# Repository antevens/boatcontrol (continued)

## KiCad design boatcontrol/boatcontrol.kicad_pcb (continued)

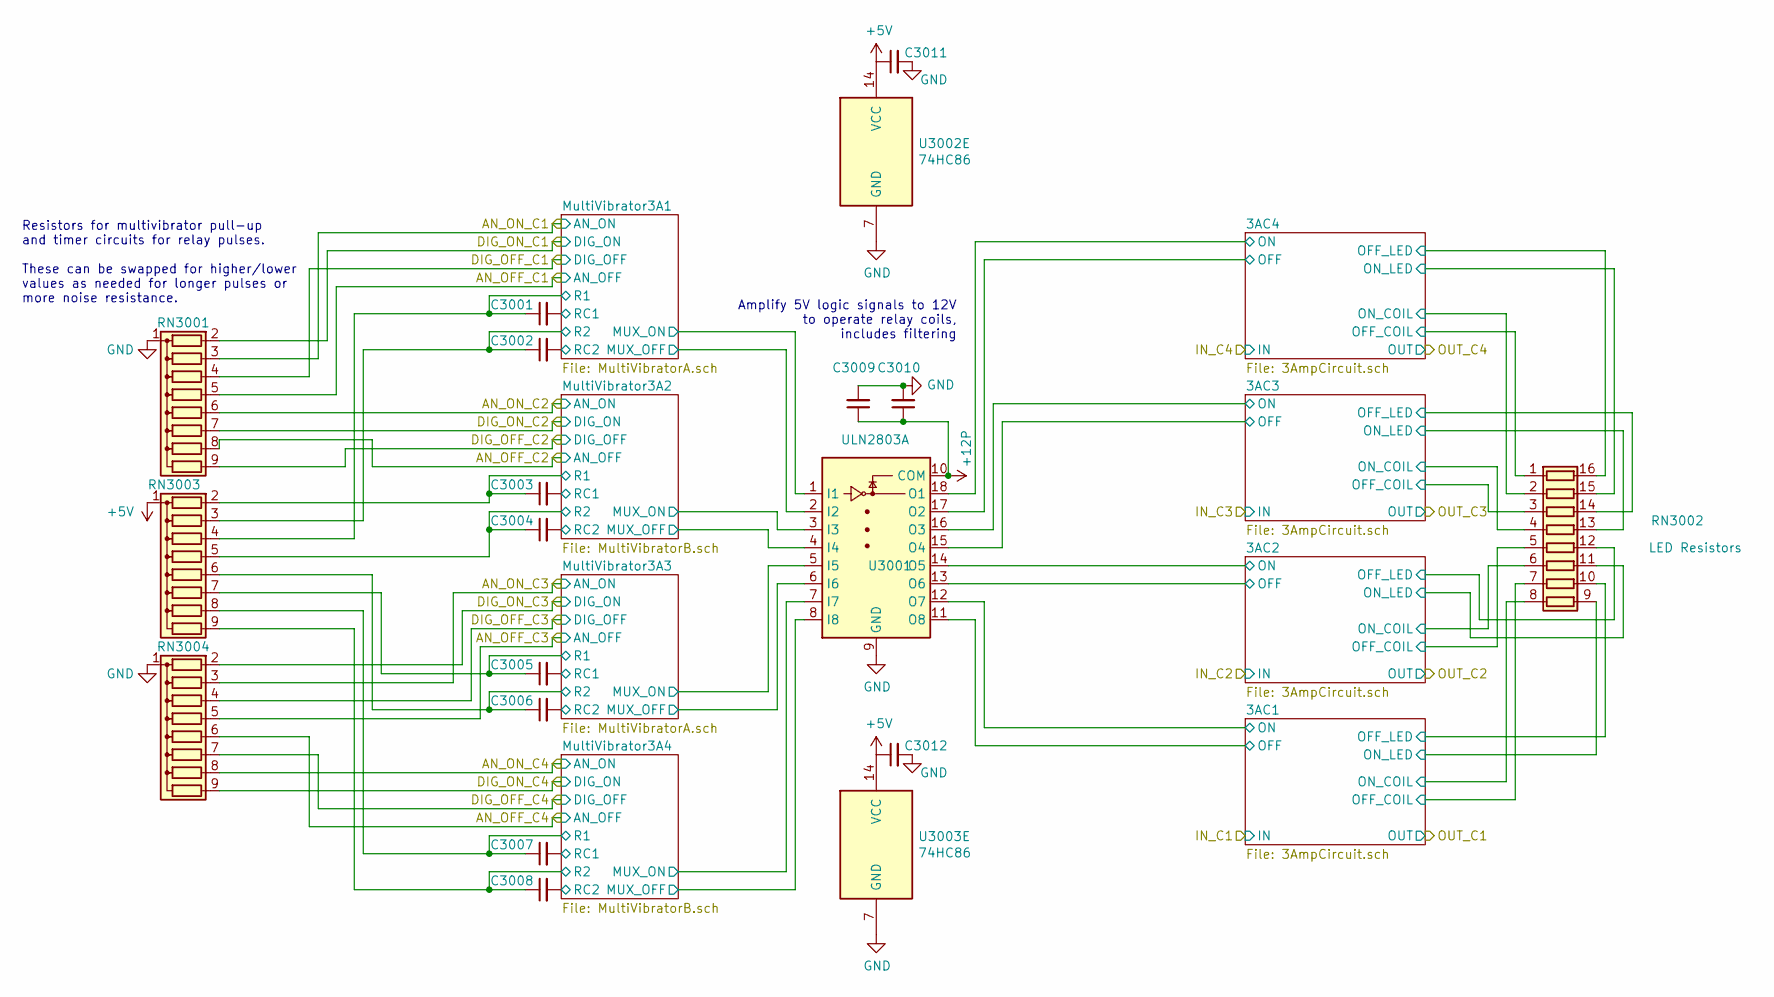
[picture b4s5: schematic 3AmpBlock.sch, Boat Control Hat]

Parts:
C1209: 10uF; C_Disc_D7.5mm_W5.0mm_P5.00mm
C1210, C1211, C1212: 0.1uF; C_Disc_D7.5mm_W5.0mm_P5.00mm
C3001, C3003, C3004, C3005, C3006, C3007, C3008: 1µF; C_Disc_D7.5mm_W5.0mm_P5.00mm
C3002: 1uF; C_Disc_D7.5mm_W5.0mm_P5.00mm
RN301, RN304: 100KΩ; R_Array_SIP9; Manufacturer_Part_Number 4609X-101-105LF
RN3002: 680Ω; DIP254P762X432-16P
RN3003: 10MΩ; R_Array_SIP9
U302, U303: 74HC86; DIP-14_W7.62mm
U3001: ULN2803A; DIP-18_W7.62mm

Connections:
12V_DC_C3_OFF: RN304.5 (R4); also elsewhere on the board
12V_DC_C3_ON: RN304.3 (R2); also elsewhere on the board
12V_DC_C4_OFF: RN304.6 (R5); also elsewhere on the board
12V_DC_C4_ON: RN304.8 (R7); also elsewhere on the board
+5V: C1211.1, C1212.1, RN3003.1 (common), U302.14 (VCC), U303.14 (VCC); also elsewhere on the board
+12P: C1209.1, C1210.1, U3001.10 (COM); also elsewhere on the board
/12V DC Common Bank/12V DC Block 1/DIG_OFF_C1: RN301.4 (R3); also elsewhere on the board
/12V DC Common Bank/12V DC Block 1/DIG_OFF_C2: RN301.9 (R8); also elsewhere on the board
/12V DC Common Bank/12V DC Block 1/DIG_OFF_C3: RN304.4 (R3); also elsewhere on the board
/12V DC Common Bank/12V DC Block 1/DIG_OFF_C4: RN304.7 (R6); also elsewhere on the board
/12V DC Common Bank/12V DC Block 1/DIG_ON_C1: RN301.2 (R1); also elsewhere on the board
/12V DC Common Bank/12V DC Block 1/DIG_ON_C2: RN301.7 (R6); also elsewhere on the board
/12V DC Common Bank/12V DC Block 1/DIG_ON_C3: RN304.2 (R1); also elsewhere on the board
/12V DC Common Bank/12V DC Block 1/DIG_ON_C4: RN304.9 (R8); also elsewhere on the board
/12V DC Common Bank/12V DC Block 4/3AC1/OFF: U3001.11 (O8); also elsewhere on the board
/12V DC Common Bank/12V DC Block 4/3AC1/OFF_COIL: RN3002.7 (R7.1); also elsewhere on the board
/12V DC Common Bank/12V DC Block 4/3AC1/OFF_LED: RN3002.10 (R7.2); also elsewhere on the board
/12V DC Common Bank/12V DC Block 4/3AC1/ON: U3001.12 (O7); also elsewhere on the board
/12V DC Common Bank/12V DC Block 4/3AC1/ON_COIL: RN3002.8 (R8.1); also elsewhere on the board
/12V DC Common Bank/12V DC Block 4/3AC1/ON_LED: RN3002.9 (R8.2); also elsewhere on the board
/12V DC Common Bank/12V DC Block 4/3AC2/OFF: U3001.13 (O6); also elsewhere on the board
/12V DC Common Bank/12V DC Block 4/3AC2/OFF_COIL: RN3002.5 (R5.1); also elsewhere on the board
/12V DC Common Bank/12V DC Block 4/3AC2/OFF_LED: RN3002.12 (R5.2); also elsewhere on the board
/12V DC Common Bank/12V DC Block 4/3AC2/ON: U3001.14 (O5); also elsewhere on the board
/12V DC Common Bank/12V DC Block 4/3AC2/ON_COIL: RN3002.6 (R6.1); also elsewhere on the board
/12V DC Common Bank/12V DC Block 4/3AC2/ON_LED: RN3002.11 (R6.2); also elsewhere on the board
/12V DC Common Bank/12V DC Block 4/3AC3/OFF: U3001.15 (O4); also elsewhere on the board
/12V DC Common Bank/12V DC Block 4/3AC3/OFF_COIL: RN3002.3 (R3.1); also elsewhere on the board
/12V DC Common Bank/12V DC Block 4/3AC3/OFF_LED: RN3002.14 (R3.2); also elsewhere on the board
/12V DC Common Bank/12V DC Block 4/3AC3/ON: U3001.16 (O3); also elsewhere on the board
/12V DC Common Bank/12V DC Block 4/3AC3/ON_COIL: RN3002.4 (R4.1); also elsewhere on the board
/12V DC Common Bank/12V DC Block 4/3AC3/ON_LED: RN3002.13 (R4.2); also elsewhere on the board
/12V DC Common Bank/12V DC Block 4/3AC4/OFF: U3001.17 (O2); also elsewhere on the board
/12V DC Common Bank/12V DC Block 4/3AC4/OFF_COIL: RN3002.1 (R1.1); also elsewhere on the board
/12V DC Common Bank/12V DC Block 4/3AC4/OFF_LED: RN3002.16 (R1.2); also elsewhere on the board
/12V DC Common Bank/12V DC Block 4/3AC4/ON: U3001.18 (O1); also elsewhere on the board
/12V DC Common Bank/12V DC Block 4/3AC4/ON_COIL: RN3002.2 (R2.1); also elsewhere on the board
/12V DC Common Bank/12V DC Block 4/3AC4/ON_LED: RN3002.15 (R2.2); also elsewhere on the board
/12V DC Common Bank/12V DC Block 4/MultiVibrator3A1/MUX_OFF: U3001.2 (I2); also elsewhere on the board
/12V DC Common Bank/12V DC Block 4/MultiVibrator3A1/MUX_ON: U3001.1 (I1); also elsewhere on the board
/12V DC Common Bank/12V DC Block 4/MultiVibrator3A1/R1: C3001.1, RN3003.4 (R3); also elsewhere on the board
/12V DC Common Bank/12V DC Block 4/MultiVibrator3A1/R2: C3002.1, RN3003.3 (R2); also elsewhere on the board
/12V DC Common Bank/12V DC Block 4/MultiVibrator3A1/RC1: C3001.2; also elsewhere on the board
/12V DC Common Bank/12V DC Block 4/MultiVibrator3A1/RC2: C3002.2; also elsewhere on the board
/12V DC Common Bank/12V DC Block 4/MultiVibrator3A2/MUX_OFF: U3001.4 (I4); also elsewhere on the board
/12V DC Common Bank/12V DC Block 4/MultiVibrator3A2/MUX_ON: U3001.3 (I3); also elsewhere on the board
/12V DC Common Bank/12V DC Block 4/MultiVibrator3A2/R1: C3003.1, RN3003.2 (R1); also elsewhere on the board
/12V DC Common Bank/12V DC Block 4/MultiVibrator3A2/R2: C3004.1, RN3003.5 (R4); also elsewhere on the board
/12V DC Common Bank/12V DC Block 4/MultiVibrator3A2/RC1: C3003.2; also elsewhere on the board
/12V DC Common Bank/12V DC Block 4/MultiVibrator3A2/RC2: C3004.2; also elsewhere on the board
/12V DC Common Bank/12V DC Block 4/MultiVibrator3A3/MUX_OFF: U3001.6 (I6); also elsewhere on the board
/12V DC Common Bank/12V DC Block 4/MultiVibrator3A3/MUX_ON: U3001.5 (I5); also elsewhere on the board
/12V DC Common Bank/12V DC Block 4/MultiVibrator3A3/R1: C3005.1, RN3003.7 (R6); also elsewhere on the board
/12V DC Common Bank/12V DC Block 4/MultiVibrator3A3/R2: C3006.1, RN3003.6 (R5); also elsewhere on the board
/12V DC Common Bank/12V DC Block 4/MultiVibrator3A3/RC1: C3005.2; also elsewhere on the board
/12V DC Common Bank/12V DC Block 4/MultiVibrator3A3/RC2: C3006.2; also elsewhere on the board
/12V DC Common Bank/12V DC Block 4/MultiVibrator3A4/MUX_OFF: U3001.8 (I8); also elsewhere on the board
/12V DC Common Bank/12V DC Block 4/MultiVibrator3A4/MUX_ON: U3001.7 (I7); also elsewhere on the board
/12V DC Common Bank/12V DC Block 4/MultiVibrator3A4/R1: C3007.1, RN3003.8 (R7); also elsewhere on the board
/12V DC Common Bank/12V DC Block 4/MultiVibrator3A4/R2: C3008.1, RN3003.9 (R8); also elsewhere on the board
/12V DC Common Bank/12V DC Block 4/MultiVibrator3A4/RC1: C3007.2; also elsewhere on the board
/12V DC Common Bank/12V DC Block 4/MultiVibrator3A4/RC2: C3008.2; also elsewhere on the board
GND: C1209.2, C1210.2, C1211.2, C1212.2, RN301.1 (common), RN304.1 (common), U302.7 (GND), U303.7 (GND), U3001.9 (GND); also elsewhere on the board

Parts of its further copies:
C301, C303, C304, C305, C306, C307, C308, C1201, C1203, C1204, C1205, C1206, C1207, C1208, C2101, C2103, C2104, C2105, C2106, C2107, C2108: 1µF; C_Disc_D7.5mm_W5.0mm_P5.00mm
C302, C1202, C2102: 1uF; C_Disc_D7.5mm_W5.0mm_P5.00mm
C309, C2109, C3009: 10uF; C_Disc_D7.5mm_W5.0mm_P5.00mm
C310, C311, C312, C2110, C2111, C2112, C3010, C3011, C3012: 0.1uF; C_Disc_D7.5mm_W5.0mm_P5.00mm
RN302, RN1202, RN2102: 680Ω; DIP254P762X432-16P
RN303, RN1203, RN2103: 10MΩ; R_Array_SIP9
RN1201, RN1204, RN2101, RN2104, RN3001, RN3004: 100KΩ; R_Array_SIP9; Manufacturer_Part_Number 4609X-101-105LF
U301, U1201, U2101: ULN2803A; DIP-18_W7.62mm
U1202, U1203, U2102, U3002, U3003: 74HC86; DIP-14_W7.62mm

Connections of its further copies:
12V_DC_C5_OFF: RN1201.5 (R4), U1202.5; also elsewhere on the board
12V_DC_C5_ON: RN1201.3 (R2), U1202.2; also elsewhere on the board
12V_DC_C6_OFF: RN1201.8 (R7), U1202.13; also elsewhere on the board
12V_DC_C6_ON: RN1201.6 (R5), U1202.10; also elsewhere on the board
12V_DC_C7_OFF: RN1204.5 (R4), U1203.5; also elsewhere on the board
12V_DC_C7_ON: RN1204.3 (R2), U1203.2; also elsewhere on the board
12V_DC_C8_OFF: RN1204.6 (R5), U1203.13; also elsewhere on the board
12V_DC_C8_ON: RN1204.8 (R7), U1203.10; also elsewhere on the board
12V_DC_C9_OFF: RN2101.5 (R4), U2102.5; also elsewhere on the board
12V_DC_C9_ON: RN2101.3 (R2), U2102.2; also elsewhere on the board
12V_DC_C10_OFF: RN2101.8 (R7), U2102.13; also elsewhere on the board
12V_DC_C10_ON: RN2101.6 (R5), U2102.10; also elsewhere on the board
12V_DC_C13_OFF: RN3001.5 (R4), U3002.5; also elsewhere on the board
12V_DC_C13_ON: RN3001.3 (R2), U3002.2; also elsewhere on the board
12V_DC_C14_OFF: RN3001.8 (R7), U3002.13; also elsewhere on the board
12V_DC_C14_ON: RN3001.6 (R5), U3002.10; also elsewhere on the board
12V_DC_C15_OFF: RN3004.5 (R4), U3003.5; also elsewhere on the board
12V_DC_C15_ON: RN3004.3 (R2), U3003.2; also elsewhere on the board
12V_DC_C16_OFF: RN3004.6 (R5), U3003.13; also elsewhere on the board
12V_DC_C16_ON: RN3004.8 (R7), U3003.10; also elsewhere on the board
+5V: C311.1, C312.1, C2111.1, C2112.1, C3011.1, C3012.1, RN303.1 (common), RN1203.1 (common), RN2103.1 (common), U1202.14 (VCC), U1203.14 (VCC), U2102.14 (VCC), U3002.14 (VCC), U3003.14 (VCC); also elsewhere on the board
+12P: C309.1, C310.1, C2109.1, C2110.1, C3009.1, C3010.1, U301.10 (COM), U1201.10 (COM), U2101.10 (COM); also elsewhere on the board
/12V DC Common Bank/12V DC Block 1/3AC1/OFF: U301.11 (O8); also elsewhere on the board
/12V DC Common Bank/12V DC Block 1/3AC1/OFF_COIL: RN302.7 (R7.1); also elsewhere on the board
/12V DC Common Bank/12V DC Block 1/3AC1/OFF_LED: RN302.10 (R7.2); also elsewhere on the board
/12V DC Common Bank/12V DC Block 1/3AC1/ON: U301.12 (O7); also elsewhere on the board
/12V DC Common Bank/12V DC Block 1/3AC1/ON_COIL: RN302.8 (R8.1); also elsewhere on the board
/12V DC Common Bank/12V DC Block 1/3AC1/ON_LED: RN302.9 (R8.2); also elsewhere on the board
/12V DC Common Bank/12V DC Block 1/3AC2/OFF: U301.13 (O6); also elsewhere on the board
/12V DC Common Bank/12V DC Block 1/3AC2/OFF_COIL: RN302.5 (R5.1); also elsewhere on the board
/12V DC Common Bank/12V DC Block 1/3AC2/OFF_LED: RN302.12 (R5.2); also elsewhere on the board
/12V DC Common Bank/12V DC Block 1/3AC2/ON: U301.14 (O5); also elsewhere on the board
/12V DC Common Bank/12V DC Block 1/3AC2/ON_COIL: RN302.6 (R6.1); also elsewhere on the board
/12V DC Common Bank/12V DC Block 1/3AC2/ON_LED: RN302.11 (R6.2); also elsewhere on the board
/12V DC Common Bank/12V DC Block 1/3AC3/OFF: U301.15 (O4); also elsewhere on the board
/12V DC Common Bank/12V DC Block 1/3AC3/OFF_COIL: RN302.3 (R3.1); also elsewhere on the board
/12V DC Common Bank/12V DC Block 1/3AC3/OFF_LED: RN302.14 (R3.2); also elsewhere on the board
/12V DC Common Bank/12V DC Block 1/3AC3/ON: U301.16 (O3); also elsewhere on the board
/12V DC Common Bank/12V DC Block 1/3AC3/ON_COIL: RN302.4 (R4.1); also elsewhere on the board
/12V DC Common Bank/12V DC Block 1/3AC3/ON_LED: RN302.13 (R4.2); also elsewhere on the board
/12V DC Common Bank/12V DC Block 1/3AC4/OFF: U301.17 (O2); also elsewhere on the board
/12V DC Common Bank/12V DC Block 1/3AC4/OFF_COIL: RN302.1 (R1.1); also elsewhere on the board
/12V DC Common Bank/12V DC Block 1/3AC4/OFF_LED: RN302.16 (R1.2); also elsewhere on the board
/12V DC Common Bank/12V DC Block 1/3AC4/ON: U301.18 (O1); also elsewhere on the board
/12V DC Common Bank/12V DC Block 1/3AC4/ON_COIL: RN302.2 (R2.1); also elsewhere on the board
/12V DC Common Bank/12V DC Block 1/3AC4/ON_LED: RN302.15 (R2.2); also elsewhere on the board
/12V DC Common Bank/12V DC Block 1/MultiVibrator3A1/MUX_OFF: U301.2 (I2); also elsewhere on the board
/12V DC Common Bank/12V DC Block 1/MultiVibrator3A1/MUX_ON: U301.1 (I1); also elsewhere on the board
/12V DC Common Bank/12V DC Block 1/MultiVibrator3A1/R1: C301.1, RN303.4 (R3); also elsewhere on the board
/12V DC Common Bank/12V DC Block 1/MultiVibrator3A1/R2: C302.1, RN303.3 (R2); also elsewhere on the board
/12V DC Common Bank/12V DC Block 1/MultiVibrator3A1/RC1: C301.2; also elsewhere on the board
/12V DC Common Bank/12V DC Block 1/MultiVibrator3A1/RC2: C302.2; also elsewhere on the board
/12V DC Common Bank/12V DC Block 1/MultiVibrator3A2/MUX_OFF: U301.4 (I4); also elsewhere on the board
/12V DC Common Bank/12V DC Block 1/MultiVibrator3A2/MUX_ON: U301.3 (I3); also elsewhere on the board
/12V DC Common Bank/12V DC Block 1/MultiVibrator3A2/R1: C303.1, RN303.2 (R1); also elsewhere on the board
/12V DC Common Bank/12V DC Block 1/MultiVibrator3A2/R2: C304.1, RN303.5 (R4); also elsewhere on the board
/12V DC Common Bank/12V DC Block 1/MultiVibrator3A2/RC1: C303.2; also elsewhere on the board
/12V DC Common Bank/12V DC Block 1/MultiVibrator3A2/RC2: C304.2; also elsewhere on the board
/12V DC Common Bank/12V DC Block 1/MultiVibrator3A3/MUX_OFF: U301.6 (I6); also elsewhere on the board
/12V DC Common Bank/12V DC Block 1/MultiVibrator3A3/MUX_ON: U301.5 (I5); also elsewhere on the board
/12V DC Common Bank/12V DC Block 1/MultiVibrator3A3/R1: C305.1, RN303.7 (R6); also elsewhere on the board
/12V DC Common Bank/12V DC Block 1/MultiVibrator3A3/R2: C306.1, RN303.6 (R5); also elsewhere on the board
/12V DC Common Bank/12V DC Block 1/MultiVibrator3A3/RC1: C305.2; also elsewhere on the board
/12V DC Common Bank/12V DC Block 1/MultiVibrator3A3/RC2: C306.2; also elsewhere on the board
/12V DC Common Bank/12V DC Block 1/MultiVibrator3A4/MUX_OFF: U301.8 (I8); also elsewhere on the board
/12V DC Common Bank/12V DC Block 1/MultiVibrator3A4/MUX_ON: U301.7 (I7); also elsewhere on the board
/12V DC Common Bank/12V DC Block 1/MultiVibrator3A4/R1: C307.1, RN303.8 (R7); also elsewhere on the board
/12V DC Common Bank/12V DC Block 1/MultiVibrator3A4/R2: C308.1, RN303.9 (R8); also elsewhere on the board
/12V DC Common Bank/12V DC Block 1/MultiVibrator3A4/RC1: C307.2; also elsewhere on the board
/12V DC Common Bank/12V DC Block 1/MultiVibrator3A4/RC2: C308.2; also elsewhere on the board
/12V DC Common Bank/12V DC Block 2/3AC1/OFF: U1201.11 (O8); also elsewhere on the board
/12V DC Common Bank/12V DC Block 2/3AC1/OFF_COIL: RN1202.7 (R7.1); also elsewhere on the board
/12V DC Common Bank/12V DC Block 2/3AC1/OFF_LED: RN1202.10 (R7.2); also elsewhere on the board
/12V DC Common Bank/12V DC Block 2/3AC1/ON: U1201.12 (O7); also elsewhere on the board
/12V DC Common Bank/12V DC Block 2/3AC1/ON_COIL: RN1202.8 (R8.1); also elsewhere on the board
/12V DC Common Bank/12V DC Block 2/3AC1/ON_LED: RN1202.9 (R8.2); also elsewhere on the board
/12V DC Common Bank/12V DC Block 2/3AC2/OFF: U1201.13 (O6); also elsewhere on the board
/12V DC Common Bank/12V DC Block 2/3AC2/OFF_COIL: RN1202.5 (R5.1); also elsewhere on the board
/12V DC Common Bank/12V DC Block 2/3AC2/OFF_LED: RN1202.12 (R5.2); also elsewhere on the board
/12V DC Common Bank/12V DC Block 2/3AC2/ON: U1201.14 (O5); also elsewhere on the board
/12V DC Common Bank/12V DC Block 2/3AC2/ON_COIL: RN1202.6 (R6.1); also elsewhere on the board
/12V DC Common Bank/12V DC Block 2/3AC2/ON_LED: RN1202.11 (R6.2); also elsewhere on the board
/12V DC Common Bank/12V DC Block 2/3AC3/OFF: U1201.15 (O4); also elsewhere on the board
/12V DC Common Bank/12V DC Block 2/3AC3/OFF_COIL: RN1202.3 (R3.1); also elsewhere on the board
/12V DC Common Bank/12V DC Block 2/3AC3/OFF_LED: RN1202.14 (R3.2); also elsewhere on the board
/12V DC Common Bank/12V DC Block 2/3AC3/ON: U1201.16 (O3); also elsewhere on the board
/12V DC Common Bank/12V DC Block 2/3AC3/ON_COIL: RN1202.4 (R4.1); also elsewhere on the board
/12V DC Common Bank/12V DC Block 2/3AC3/ON_LED: RN1202.13 (R4.2); also elsewhere on the board
/12V DC Common Bank/12V DC Block 2/3AC4/OFF: U1201.17 (O2); also elsewhere on the board
/12V DC Common Bank/12V DC Block 2/3AC4/OFF_COIL: RN1202.1 (R1.1); also elsewhere on the board
/12V DC Common Bank/12V DC Block 2/3AC4/OFF_LED: RN1202.16 (R1.2); also elsewhere on the board
/12V DC Common Bank/12V DC Block 2/3AC4/ON: U1201.18 (O1); also elsewhere on the board
/12V DC Common Bank/12V DC Block 2/3AC4/ON_COIL: RN1202.2 (R2.1); also elsewhere on the board
/12V DC Common Bank/12V DC Block 2/3AC4/ON_LED: RN1202.15 (R2.2); also elsewhere on the board
/12V DC Common Bank/12V DC Block 2/DIG_OFF_C1: RN1201.4 (R3), U1202.4; also elsewhere on the board
/12V DC Common Bank/12V DC Block 2/DIG_OFF_C2: RN1201.9 (R8), U1202.12; also elsewhere on the board
/12V DC Common Bank/12V DC Block 2/DIG_OFF_C3: RN1204.4 (R3), U1203.4; also elsewhere on the board
/12V DC Common Bank/12V DC Block 2/DIG_OFF_C4: RN1204.7 (R6), U1203.12; also elsewhere on the board
/12V DC Common Bank/12V DC Block 2/DIG_ON_C1: RN1201.2 (R1), U1202.1; also elsewhere on the board
/12V DC Common Bank/12V DC Block 2/DIG_ON_C2: RN1201.7 (R6), U1202.9; also elsewhere on the board
/12V DC Common Bank/12V DC Block 2/DIG_ON_C3: RN1204.2 (R1), U1203.1; also elsewhere on the board
/12V DC Common Bank/12V DC Block 2/DIG_ON_C4: RN1204.9 (R8), U1203.9; also elsewhere on the board
/12V DC Common Bank/12V DC Block 2/MultiVibrator3A1/MUX_OFF: U1201.2 (I2); also elsewhere on the board
/12V DC Common Bank/12V DC Block 2/MultiVibrator3A1/MUX_ON: U1201.1 (I1); also elsewhere on the board
/12V DC Common Bank/12V DC Block 2/MultiVibrator3A1/R1: C1201.1, RN1203.4 (R3); also elsewhere on the board
/12V DC Common Bank/12V DC Block 2/MultiVibrator3A1/R2: C1202.1, RN1203.3 (R2); also elsewhere on the board
/12V DC Common Bank/12V DC Block 2/MultiVibrator3A1/RC1: C1201.2; also elsewhere on the board
/12V DC Common Bank/12V DC Block 2/MultiVibrator3A1/RC2: C1202.2; also elsewhere on the board
/12V DC Common Bank/12V DC Block 2/MultiVibrator3A2/MUX_OFF: U1201.4 (I4); also elsewhere on the board
/12V DC Common Bank/12V DC Block 2/MultiVibrator3A2/MUX_ON: U1201.3 (I3); also elsewhere on the board
/12V DC Common Bank/12V DC Block 2/MultiVibrator3A2/R1: C1203.1, RN1203.2 (R1); also elsewhere on the board
/12V DC Common Bank/12V DC Block 2/MultiVibrator3A2/R2: C1204.1, RN1203.5 (R4); also elsewhere on the board
/12V DC Common Bank/12V DC Block 2/MultiVibrator3A2/RC1: C1203.2; also elsewhere on the board
/12V DC Common Bank/12V DC Block 2/MultiVibrator3A2/RC2: C1204.2; also elsewhere on the board
/12V DC Common Bank/12V DC Block 2/MultiVibrator3A3/MUX_OFF: U1201.6 (I6); also elsewhere on the board
/12V DC Common Bank/12V DC Block 2/MultiVibrator3A3/MUX_ON: U1201.5 (I5); also elsewhere on the board
/12V DC Common Bank/12V DC Block 2/MultiVibrator3A3/R1: C1205.1, RN1203.7 (R6); also elsewhere on the board
/12V DC Common Bank/12V DC Block 2/MultiVibrator3A3/R2: C1206.1, RN1203.6 (R5); also elsewhere on the board
/12V DC Common Bank/12V DC Block 2/MultiVibrator3A3/RC1: C1205.2; also elsewhere on the board
/12V DC Common Bank/12V DC Block 2/MultiVibrator3A3/RC2: C1206.2; also elsewhere on the board
/12V DC Common Bank/12V DC Block 2/MultiVibrator3A4/MUX_OFF: U1201.8 (I8); also elsewhere on the board
/12V DC Common Bank/12V DC Block 2/MultiVibrator3A4/MUX_ON: U1201.7 (I7); also elsewhere on the board
/12V DC Common Bank/12V DC Block 2/MultiVibrator3A4/R1: C1207.1, RN1203.8 (R7); also elsewhere on the board
/12V DC Common Bank/12V DC Block 2/MultiVibrator3A4/R2: C1208.1, RN1203.9 (R8); also elsewhere on the board
/12V DC Common Bank/12V DC Block 2/MultiVibrator3A4/RC1: C1207.2; also elsewhere on the board
/12V DC Common Bank/12V DC Block 2/MultiVibrator3A4/RC2: C1208.2; also elsewhere on the board
/12V DC Common Bank/12V DC Block 3/3AC1/OFF: U2101.11 (O8); also elsewhere on the board
/12V DC Common Bank/12V DC Block 3/3AC1/OFF_COIL: RN2102.7 (R7.1); also elsewhere on the board
/12V DC Common Bank/12V DC Block 3/3AC1/OFF_LED: RN2102.10 (R7.2); also elsewhere on the board
/12V DC Common Bank/12V DC Block 3/3AC1/ON: U2101.12 (O7); also elsewhere on the board
/12V DC Common Bank/12V DC Block 3/3AC1/ON_COIL: RN2102.8 (R8.1); also elsewhere on the board
/12V DC Common Bank/12V DC Block 3/3AC1/ON_LED: RN2102.9 (R8.2); also elsewhere on the board
/12V DC Common Bank/12V DC Block 3/3AC2/OFF: U2101.13 (O6); also elsewhere on the board
/12V DC Common Bank/12V DC Block 3/3AC2/OFF_COIL: RN2102.5 (R5.1); also elsewhere on the board
/12V DC Common Bank/12V DC Block 3/3AC2/OFF_LED: RN2102.12 (R5.2); also elsewhere on the board
/12V DC Common Bank/12V DC Block 3/3AC2/ON: U2101.14 (O5); also elsewhere on the board
/12V DC Common Bank/12V DC Block 3/3AC2/ON_COIL: RN2102.6 (R6.1); also elsewhere on the board
/12V DC Common Bank/12V DC Block 3/3AC2/ON_LED: RN2102.11 (R6.2); also elsewhere on the board
/12V DC Common Bank/12V DC Block 3/3AC3/OFF: U2101.15 (O4); also elsewhere on the board
/12V DC Common Bank/12V DC Block 3/3AC3/OFF_COIL: RN2102.3 (R3.1); also elsewhere on the board
/12V DC Common Bank/12V DC Block 3/3AC3/OFF_LED: RN2102.14 (R3.2); also elsewhere on the board
/12V DC Common Bank/12V DC Block 3/3AC3/ON: U2101.16 (O3); also elsewhere on the board
/12V DC Common Bank/12V DC Block 3/3AC3/ON_COIL: RN2102.4 (R4.1); also elsewhere on the board
/12V DC Common Bank/12V DC Block 3/3AC3/ON_LED: RN2102.13 (R4.2); also elsewhere on the board
/12V DC Common Bank/12V DC Block 3/3AC4/OFF: U2101.17 (O2); also elsewhere on the board
/12V DC Common Bank/12V DC Block 3/3AC4/OFF_COIL: RN2102.1 (R1.1); also elsewhere on the board
/12V DC Common Bank/12V DC Block 3/3AC4/OFF_LED: RN2102.16 (R1.2); also elsewhere on the board
/12V DC Common Bank/12V DC Block 3/3AC4/ON: U2101.18 (O1); also elsewhere on the board
/12V DC Common Bank/12V DC Block 3/3AC4/ON_COIL: RN2102.2 (R2.1); also elsewhere on the board
/12V DC Common Bank/12V DC Block 3/3AC4/ON_LED: RN2102.15 (R2.2); also elsewhere on the board
/12V DC Common Bank/12V DC Block 3/DIG_OFF_C1: RN2101.4 (R3), U2102.4; also elsewhere on the board
/12V DC Common Bank/12V DC Block 3/DIG_OFF_C2: RN2101.9 (R8), U2102.12; also elsewhere on the board
/12V DC Common Bank/12V DC Block 3/DIG_OFF_C3: RN2104.4 (R3); also elsewhere on the board
/12V DC Common Bank/12V DC Block 3/DIG_OFF_C4: RN2104.7 (R6); also elsewhere on the board
/12V DC Common Bank/12V DC Block 3/DIG_ON_C1: RN2101.2 (R1), U2102.1; also elsewhere on the board
/12V DC Common Bank/12V DC Block 3/DIG_ON_C2: RN2101.7 (R6), U2102.9; also elsewhere on the board
/12V DC Common Bank/12V DC Block 3/DIG_ON_C3: RN2104.2 (R1); also elsewhere on the board
/12V DC Common Bank/12V DC Block 3/DIG_ON_C4: RN2104.9 (R8); also elsewhere on the board
/12V DC Common Bank/12V DC Block 3/MultiVibrator3A1/MUX_OFF: U2101.2 (I2); also elsewhere on the board
/12V DC Common Bank/12V DC Block 3/MultiVibrator3A1/MUX_ON: U2101.1 (I1); also elsewhere on the board
/12V DC Common Bank/12V DC Block 3/MultiVibrator3A1/R1: C2101.1, RN2103.4 (R3); also elsewhere on the board
/12V DC Common Bank/12V DC Block 3/MultiVibrator3A1/R2: C2102.1, RN2103.3 (R2); also elsewhere on the board
/12V DC Common Bank/12V DC Block 3/MultiVibrator3A1/RC1: C2101.2; also elsewhere on the board
/12V DC Common Bank/12V DC Block 3/MultiVibrator3A1/RC2: C2102.2; also elsewhere on the board
/12V DC Common Bank/12V DC Block 3/MultiVibrator3A2/MUX_OFF: U2101.4 (I4); also elsewhere on the board
/12V DC Common Bank/12V DC Block 3/MultiVibrator3A2/MUX_ON: U2101.3 (I3); also elsewhere on the board
/12V DC Common Bank/12V DC Block 3/MultiVibrator3A2/R1: C2103.1, RN2103.2 (R1); also elsewhere on the board
/12V DC Common Bank/12V DC Block 3/MultiVibrator3A2/R2: C2104.1, RN2103.5 (R4); also elsewhere on the board
/12V DC Common Bank/12V DC Block 3/MultiVibrator3A2/RC1: C2103.2; also elsewhere on the board
/12V DC Common Bank/12V DC Block 3/MultiVibrator3A2/RC2: C2104.2; also elsewhere on the board
/12V DC Common Bank/12V DC Block 3/MultiVibrator3A3/MUX_OFF: U2101.6 (I6); also elsewhere on the board
/12V DC Common Bank/12V DC Block 3/MultiVibrator3A3/MUX_ON: U2101.5 (I5); also elsewhere on the board
/12V DC Common Bank/12V DC Block 3/MultiVibrator3A3/R1: C2105.1, RN2103.7 (R6); also elsewhere on the board
/12V DC Common Bank/12V DC Block 3/MultiVibrator3A3/R2: C2106.1, RN2103.6 (R5); also elsewhere on the board
/12V DC Common Bank/12V DC Block 3/MultiVibrator3A3/RC1: C2105.2; also elsewhere on the board
/12V DC Common Bank/12V DC Block 3/MultiVibrator3A3/RC2: C2106.2; also elsewhere on the board
/12V DC Common Bank/12V DC Block 3/MultiVibrator3A4/MUX_OFF: U2101.8 (I8); also elsewhere on the board
/12V DC Common Bank/12V DC Block 3/MultiVibrator3A4/MUX_ON: U2101.7 (I7); also elsewhere on the board
/12V DC Common Bank/12V DC Block 3/MultiVibrator3A4/R1: C2107.1, RN2103.8 (R7); also elsewhere on the board
/12V DC Common Bank/12V DC Block 3/MultiVibrator3A4/R2: C2108.1, RN2103.9 (R8); also elsewhere on the board
/12V DC Common Bank/12V DC Block 3/MultiVibrator3A4/RC1: C2107.2; also elsewhere on the board
/12V DC Common Bank/12V DC Block 3/MultiVibrator3A4/RC2: C2108.2; also elsewhere on the board
/12V DC Common Bank/12V DC Block 4/DIG_OFF_C1: RN3001.4 (R3), U3002.4; also elsewhere on the board
/12V DC Common Bank/12V DC Block 4/DIG_OFF_C2: RN3001.9 (R8), U3002.12; also elsewhere on the board
/12V DC Common Bank/12V DC Block 4/DIG_OFF_C3: RN3004.4 (R3), U3003.4; also elsewhere on the board
/12V DC Common Bank/12V DC Block 4/DIG_OFF_C4: RN3004.7 (R6), U3003.12; also elsewhere on the board
/12V DC Common Bank/12V DC Block 4/DIG_ON_C1: RN3001.2 (R1), U3002.1; also elsewhere on the board
/12V DC Common Bank/12V DC Block 4/DIG_ON_C2: RN3001.7 (R6), U3002.9; also elsewhere on the board
/12V DC Common Bank/12V DC Block 4/DIG_ON_C3: RN3004.2 (R1), U3003.1; also elsewhere on the board
/12V DC Common Bank/12V DC Block 4/DIG_ON_C4: RN3004.9 (R8), U3003.9; also elsewhere on the board
GND: C309.2, C310.2, C311.2, C312.2, C2109.2, C2110.2, C2111.2, C2112.2, C3009.2, C3010.2, C3011.2, C3012.2, RN1201.1 (common), RN1204.1 (common), RN2101.1 (common), RN2104.1 (common), RN3001.1 (common), RN3004.1 (common), U301.9 (GND), U1201.9 (GND), U1202.7 (GND), U1203.7 (GND), U2101.9 (GND), U2102.7 (GND), U3002.7 (GND), U3003.7 (GND); also elsewhere on the board
unnamed 934: U1202.3; also elsewhere on the board
unnamed 935: U1202.6; also elsewhere on the board
unnamed 938: U1202.8; also elsewhere on the board
unnamed 939: U1202.11; also elsewhere on the board
unnamed 942: U1203.3; also elsewhere on the board
unnamed 943: U1203.6; also elsewhere on the board
unnamed 946: U1203.8; also elsewhere on the board
unnamed 947: U1203.11; also elsewhere on the board
unnamed 950: U2102.3; also elsewhere on the board
unnamed 951: U2102.6; also elsewhere on the board
unnamed 954: U2102.8; also elsewhere on the board
unnamed 955: U2102.11; also elsewhere on the board
unnamed 964: U3002.3; also elsewhere on the board
unnamed 965: U3002.6; also elsewhere on the board
unnamed 968: U3002.8; also elsewhere on the board
unnamed 969: U3002.11; also elsewhere on the board
unnamed 972: U3003.3; also elsewhere on the board
unnamed 973: U3003.6; also elsewhere on the board
unnamed 976: U3003.8; also elsewhere on the board
unnamed 977: U3003.11; also elsewhere on the board

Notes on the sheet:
Amplify 5V logic signals to 12V to operate relay coils, includes filtering
Resistors for multivibrator pull-up and timer circuits for relay pulses. These can be swapped for higher/lower values as needed for longer pulses or more noise resistance.
